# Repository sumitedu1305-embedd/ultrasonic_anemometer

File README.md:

ORTHOGONAL CONFIGURATION - NEW PCB

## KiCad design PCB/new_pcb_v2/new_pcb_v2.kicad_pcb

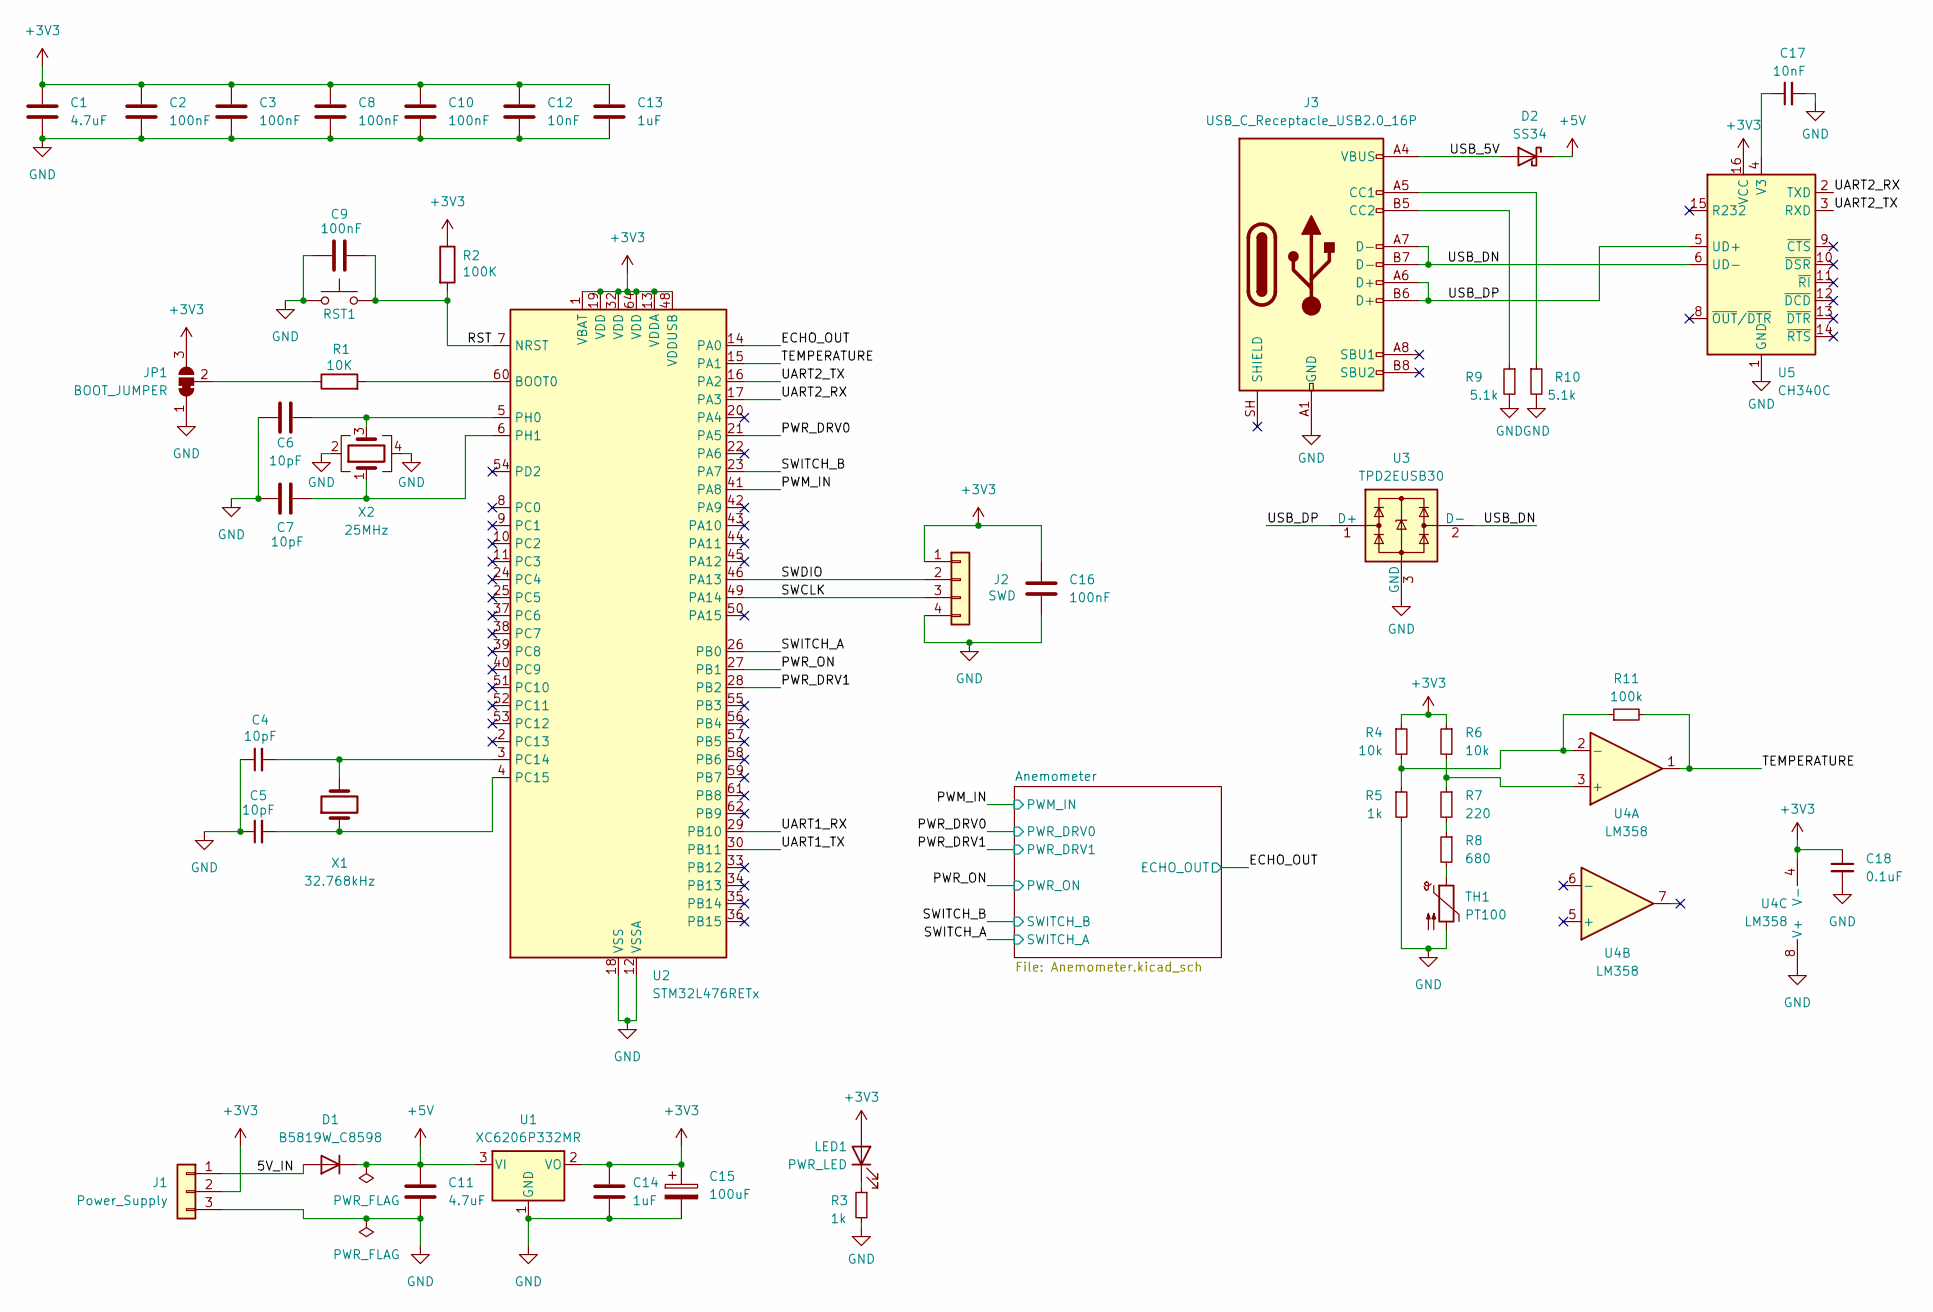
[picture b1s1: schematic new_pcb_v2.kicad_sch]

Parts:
C1, C11: 4.7uF; C_0603_1608Metric
C2, C3, C8, C9, C10, C16: 100nF; C_0402_1005Metric
C4, C5, C6, C7: 10pF; C_0402_1005Metric
C12: 10nF; C_0402_1005Metric
C13, C14: 1uF; C_0402_1005Metric
C15: 100uF; CP_EIA-3528-12_Kemet-T
C17: 10nF; C_0603_1608Metric
C18: 0.1uF; C_0603_1608Metric
D1: B5819W_C8598; D_SOD-123
D2: SS34; D_SMA
J1: Power_Supply; PinHeader_1x03_P2.54mm_Vertical
J2: SWD; PinHeader_1x04_P2.54mm_Vertical
J3: USB_C_Receptacle_USB2.0_16P; USB_C_Receptacle_G-Switch_GT-USB-7010ASV
JP1: BOOT_JUMPER; SolderJumper-3_P1.3mm_Bridged12_RoundedPad1.0x1.5mm_NumberL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
LED1: PWR_LED; LED_0603_1608Metric
R1: 10K; R_0603_1608Metric
R2: 100K; R_0603_1608Metric
R3, R5: 1k; R_0603_1608Metric
R4, R6: 10k; R_0603_1608Metric
R7: 220; R_0603_1608Metric
R8: 680; R_0603_1608Metric
R9, R10: 5.1k; R_0603_1608Metric
R11: 100k; R_0603_1608Metric
RST1: SW_Push; SW_SPST_B3U-1000P
TH1: PT100; TO-92-2
U1: XC6206P332MR; SOT-23-3
U2: STM32L476RETx; LQFP-64_10x10mm_P0.5mm
U3: TPD2EUSB30; Texas_DRT-3
U4: LM358; SO-8_3.9x4.9mm_P1.27mm
U5: CH340C; SOIC-16_3.9x9.9mm_P1.27mm
X1: 32.768kHz; Crystal_SMD_2012-2Pin_2.0x1.2mm
X2: 25MHz; Oscillator_SMD_Abracon_ASE-4Pin_3.2x2.5mm

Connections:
+3V3: C1.1, C2.1, C3.1, C8.1, C10.1, C12.1, C13.1, C14.1, C15.1, C16.1, C18.1, J1.2, J2.1, JP1.3 (B), LED1.2 (A), R2.1, R4.1, R6.1, U1.2 (VO), U2.1 (VBAT), U2.13 (VDDA), U2.19 (VDD), U2.32 (VDD), U2.48 (VDDUSB), U2.64 (VDD), U4.4 (V-), U5.16 (VCC); also elsewhere on the board
+5V: C11.1, D1.1 (K), D2.1 (K), U1.3 (VI)
/5V_IN: D1.2 (A), J1.1; also elsewhere on the board
/ECHO_OUT: U2.14 (PA0); also elsewhere on the board
/PWM_IN: U2.41 (PA8); also elsewhere on the board
/PWR_DRV0: U2.21 (PA5); also elsewhere on the board
/PWR_DRV1: U2.28 (PB2); also elsewhere on the board
/PWR_ON: U2.27 (PB1); also elsewhere on the board
/RST: C9.2, R2.2, RST1.2, U2.7 (NRST)
/SWCLK: J2.3, U2.49 (PA14); also elsewhere on the board
/SWDIO: J2.2, U2.46 (PA13); also elsewhere on the board
/SWITCH_A: U2.26 (PB0); also elsewhere on the board
/SWITCH_B: U2.23 (PA7); also elsewhere on the board
/TEMPERATURE: R11.2, U2.15 (PA1), U4.1
/UART1_RX: U2.29 (PB10)
/UART1_TX: U2.30 (PB11)
/UART2_RX: U2.17 (PA3), U5.2 (TXD)
/UART2_TX: U2.16 (PA2), U5.3 (RXD)
/USB_5V: D2.2 (A), J3.A4 (VBUS), J3.A9 (VBUS), J3.B4 (VBUS), J3.B9 (VBUS)
/USB_DN: J3.A7 (D-), J3.B7 (D-), U3.2 (D-), U5.6 (UD-)
/USB_DP: J3.A6 (D+), J3.B6 (D+), U3.1 (D+), U5.5 (UD+)
GND: C1.2, C2.2, C3.2, C4.1, C5.1, C6.1, C7.1, C8.2, C9.1, C10.2, C11.2, C12.2, C13.2, C14.2, C15.2, C16.2, C17.2, C18.2, J1.3, J2.4, J3.A1 (GND), J3.A12 (GND), J3.B1 (GND), J3.B12 (GND), JP1.1 (A), R3.2, R5.2, R9.2, R10.2, RST1.1, TH1.2, U1.1 (GND), U2.12 (VSSA), U2.18 (VSS), U2.31 (VSS), U2.47 (VSS), U2.63 (VSS), U3.3 (GND), U4.8 (V+), U5.1 (GND), X2.2, X2.4; also elsewhere on the board
unnamed: J3.A5 (CC1), R10.1
unnamed: J3.B5 (CC2), R9.1
unnamed: JP1.2 (C), R1.1
unnamed: LED1.1 (K), R3.1
unnamed: R7.2, R8.1
unnamed 49: R8.2, TH1.1; also elsewhere on the board
unnamed: R1.2, U2.60 (BOOT0)
unnamed: C4.2, U2.3 (PC14), X1.2
unnamed: C5.2, U2.4 (PC15), X1.1
unnamed: C6.2, U2.5 (PH0), X2.3
unnamed: C7.2, U2.6 (PH1), X2.1
unnamed: R6.2, R7.1, U4.3 (+)
unnamed: R4.2, R5.1, R11.1, U4.2 (-)
unnamed: C17.1, U5.4 (V3)

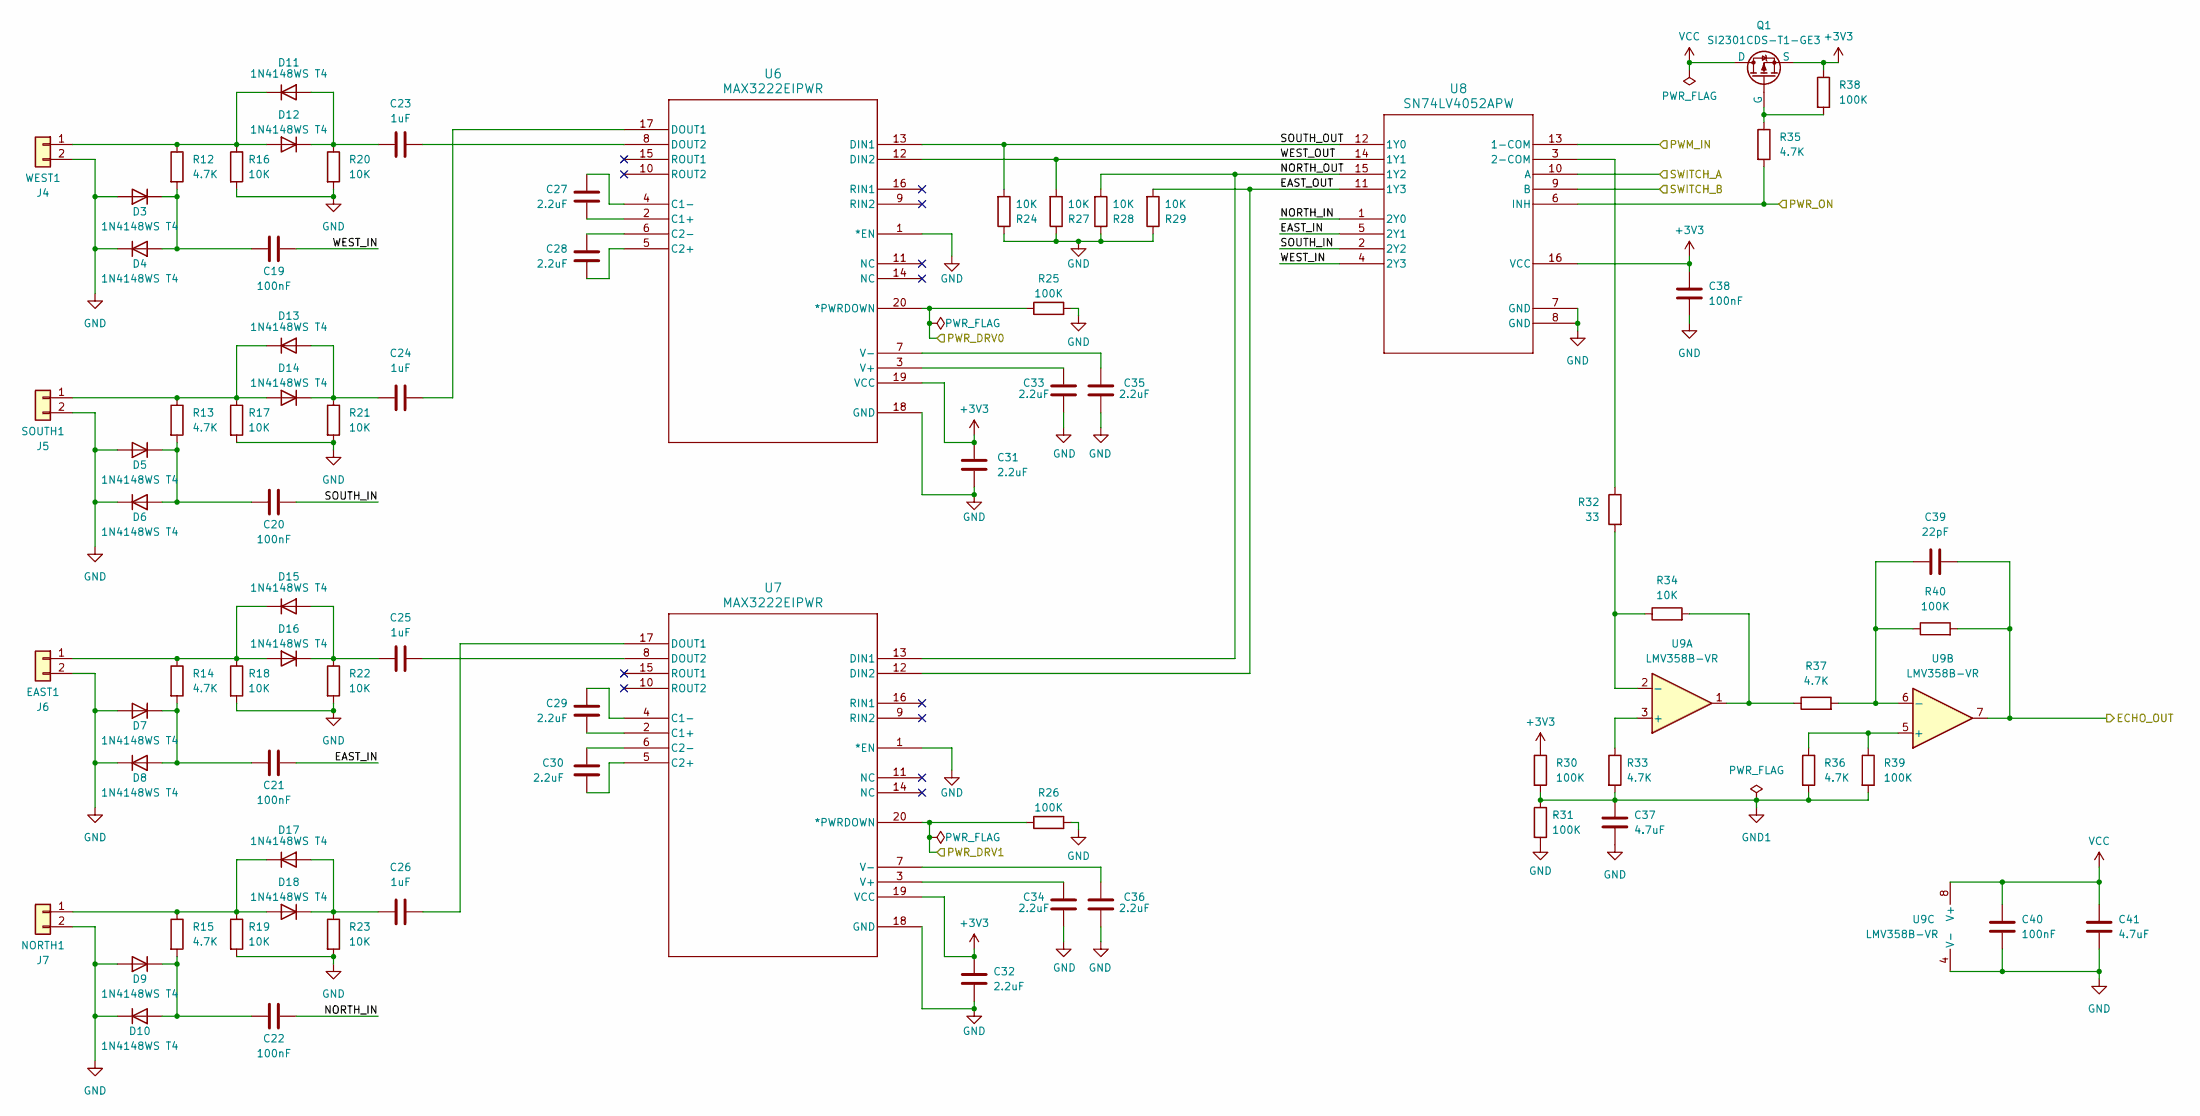
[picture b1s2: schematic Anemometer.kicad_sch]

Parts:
C19, C20, C21, C22, C40: 100nF; C_0402_1005Metric
C23, C24, C25, C26: 1uF; C_0603_1608Metric
C27, C28, C29, C30, C31, C32, C33, C34, C35, C36: 2.2uF; C_0603_1608Metric
C37: 4.7uF; C_0402_1005Metric
C38: 100nF; C_0603_1608Metric
C39: 22pF; C_0402_1005Metric
C41: 4.7uF; C_0603_1608Metric
D3, D4, D5, D6, D7, D8, D9, D10, D11, D12, D13, D14, D15, D16, D17, D18: 1N4148WS T4; D_SOD-323
J4: WEST1; JST_PH_B2B-PH-K_1x02_P2.00mm_Vertical
J5: SOUTH1; JST_PH_B2B-PH-K_1x02_P2.00mm_Vertical
J6: EAST1; JST_PH_B2B-PH-K_1x02_P2.00mm_Vertical
J7: NORTH1; JST_PH_B2B-PH-K_1x02_P2.00mm_Vertical
Q1: SI2301CDS-T1-GE3; SOT-23-3
R12, R13, R14, R15, R33, R35, R36, R37: 4.7K; R_0402_1005Metric
R16, R17, R18, R19, R20, R21, R22, R23, R24, R27, R28, R29, R34: 10K; R_0402_1005Metric
R25, R26, R30, R31, R38, R39, R40: 100K; R_0402_1005Metric
R32: 33; R_0402_1005Metric
U6, U7: MAX3222EIPWR; TSSOP-20_4.4x6.5mm_P0.65mm
U8: SN74LV4052APW; TSSOP-16_4.4x5mm_P0.65mm
U9: LMV358B-VR; MSOP-8_3x3mm_P0.65mm

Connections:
+3V3: C31.1, C32.1, C38.1, Q1.2 (S), R30.1, R38.1, U6.19 (VCC), U7.19 (VCC), U8.16 (VCC); also elsewhere on the board
/Anemometer/EAST_IN: C21.2, U8.5 (2Y1)
/Anemometer/EAST_OUT: R29.2, U7.12 (DIN2), U8.11 (1Y3)
/Anemometer/NORTH_IN: C22.2, U8.1 (2Y0)
/Anemometer/NORTH_OUT: R28.2, U7.13 (DIN1), U8.15 (1Y2)
/Anemometer/SOUTH_IN: C20.2, U8.2 (2Y2)
/Anemometer/SOUTH_OUT: R24.2, U6.13 (DIN1), U8.12 (1Y0)
/Anemometer/WEST_IN: C19.2, U8.4 (2Y3)
/Anemometer/WEST_OUT: R27.2, U6.12 (DIN2), U8.14 (1Y1)
/ECHO_OUT: C39.2, R40.2, U9.7; also elsewhere on the board
/PWM_IN: U8.13 (1-COM); also elsewhere on the board
/PWR_DRV0: R25.1, U6.20 (*PWRDOWN); also elsewhere on the board
/PWR_DRV1: R26.1, U7.20 (*PWRDOWN); also elsewhere on the board
/PWR_ON: R35.2, U8.6 (INH); also elsewhere on the board
/SWITCH_A: U8.10 (A); also elsewhere on the board
/SWITCH_B: U8.9 (B); also elsewhere on the board
GND: C31.2, C32.2, C33.1, C34.1, C35.1, C36.1, C37.2, C38.2, C40.2, C41.2, D3.2 (A), D4.1 (K), D5.2 (A), D6.1 (K), D7.2 (A), D8.1 (K), D9.2 (A), D10.1 (K), J4.2, J5.2, J6.2, J7.2, R16.2, R17.2, R18.2, R19.2, R20.2, R21.2, R22.2, R23.2, R24.1, R25.2, R26.2, R27.1, R28.1, R29.1, R31.2, U6.1 (*EN), U6.18 (GND), U7.1 (*EN), U7.18 (GND), U8.7 (GND), U8.8 (GND), U9.4 (V-); also elsewhere on the board
GND1: C37.1, R30.2, R31.1, R33.2, R36.2, R39.2
unnamed: C19.1, D3.1 (K), D4.2 (A), R12.2
unnamed: C20.1, D5.1 (K), D6.2 (A), R13.2
unnamed: C21.1, D7.1 (K), D8.2 (A), R14.2
unnamed: C22.1, D9.1 (K), D10.2 (A), R15.2
unnamed: C23.1, D11.2 (A), D12.1 (K), R20.1
unnamed 36: D11.1 (K), D12.2 (A), J4.1, R12.1, R16.1; also elsewhere on the board
unnamed: C24.1, D13.2 (A), D14.1 (K), R21.1
unnamed 38: D13.1 (K), D14.2 (A), J5.1, R13.1, R17.1; also elsewhere on the board
unnamed: C25.1, D15.2 (A), D16.1 (K), R22.1
unnamed 40: D15.1 (K), D16.2 (A), J6.1, R14.1, R18.1; also elsewhere on the board
unnamed: C26.1, D17.2 (A), D18.1 (K), R23.1
unnamed 42: D17.1 (K), D18.2 (A), J7.1, R15.1, R19.1; also elsewhere on the board
unnamed: Q1.1 (G), R35.1, R38.2
unnamed: R34.2, R37.1, U9.1
unnamed: C27.2, U6.2 (C1+)
unnamed: C27.1, U6.4 (C1-)
unnamed: C28.1, U6.5 (C2+)
unnamed: C28.2, U6.6 (C2-)
unnamed: C24.2, U6.17 (DOUT1)
unnamed: C23.2, U6.8 (DOUT2)
unnamed: C33.2, U6.3 (V+)
unnamed: C35.2, U6.7 (V-)
unnamed: C29.2, U7.2 (C1+)
unnamed: C29.1, U7.4 (C1-)
unnamed: C30.1, U7.5 (C2+)
unnamed: C30.2, U7.6 (C2-)
unnamed: C26.2, U7.17 (DOUT1)
unnamed: C25.2, U7.8 (DOUT2)
unnamed: C34.2, U7.3 (V+)
unnamed: C36.2, U7.7 (V-)
unnamed: R32.1, U8.3 (2-COM)
unnamed: R33.1, U9.3 (+)
unnamed: R32.2, R34.1, U9.2 (-)
unnamed: R36.1, R39.1, U9.5 (+)
unnamed: C39.1, R37.2, R40.1, U9.6 (-)
VCC: C40.1, C41.1, Q1.3 (D), U9.8 (V+)

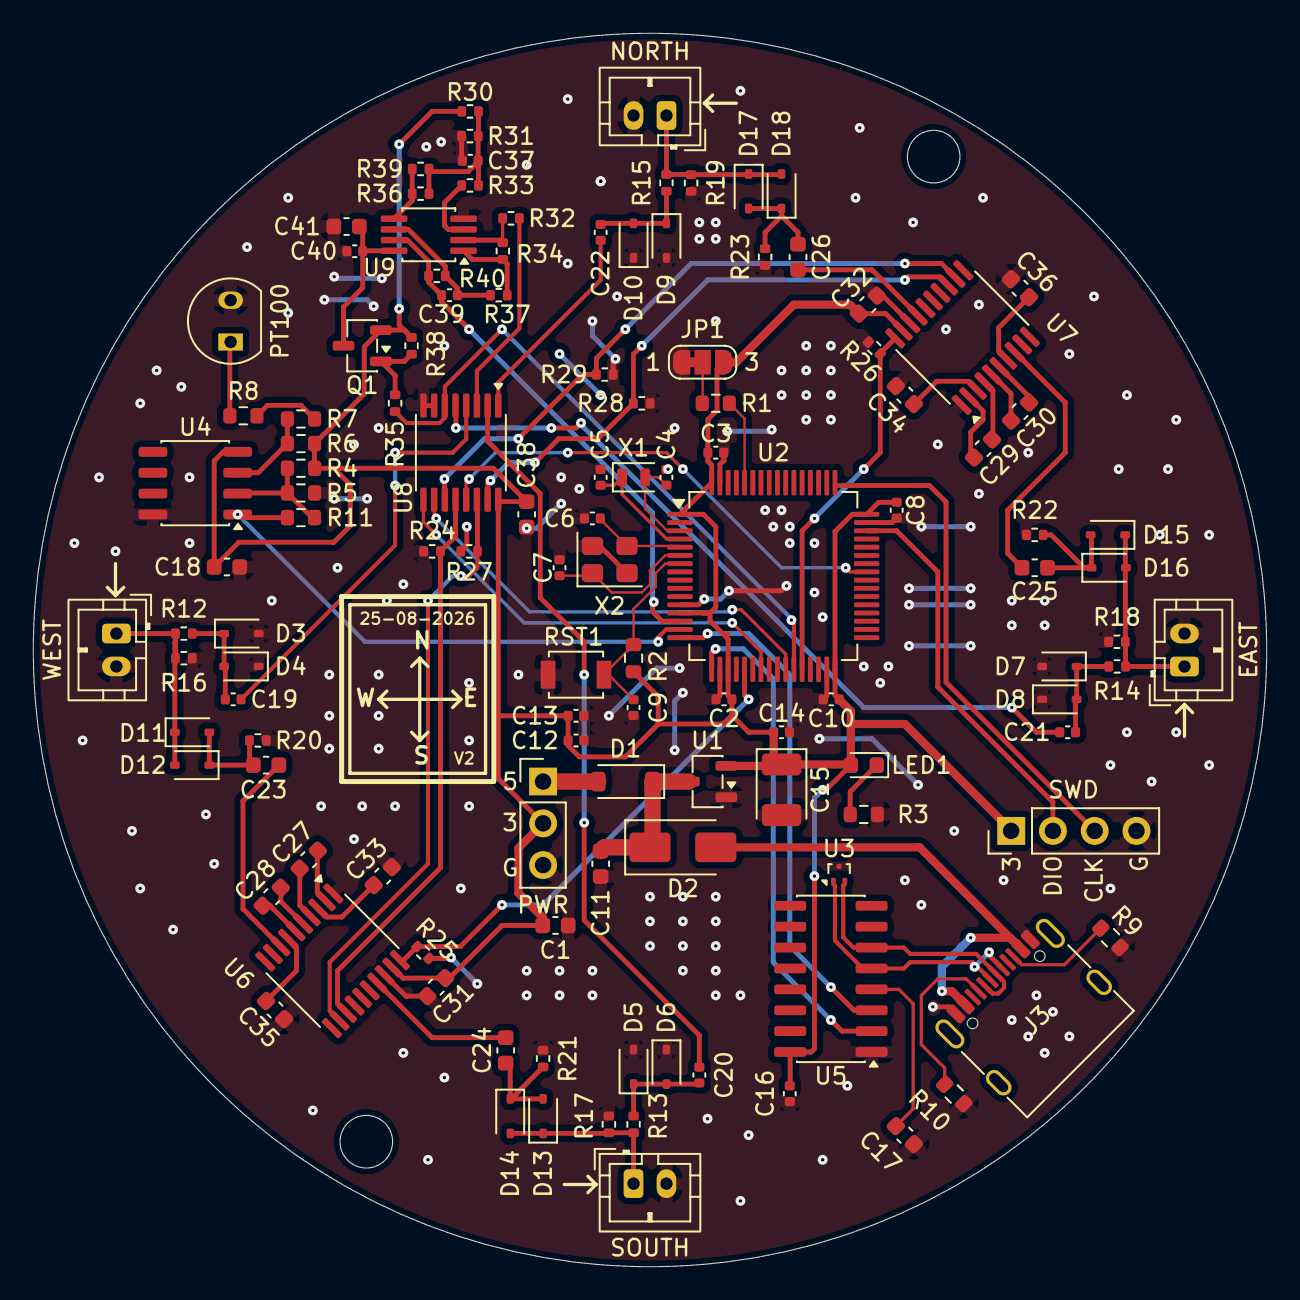
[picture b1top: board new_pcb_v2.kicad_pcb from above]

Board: 2 copper layers, 75.0 x 75.0 mm, 122 parts (0 on the bottom side), 79 nets.

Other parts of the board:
EAST: EAST1; JST_PH_B2B-PH-K_1x02_P2.00mm_Vertical
NORTH: NORTH1; JST_PH_B2B-PH-K_1x02_P2.00mm_Vertical
PT100: PT100; TO-92-2
PWR: Power_Supply; PinHeader_1x03_P2.54mm_Vertical
SOUTH: SOUTH1; JST_PH_B2B-PH-K_1x02_P2.00mm_Vertical
SWD: SWD; PinHeader_1x04_P2.54mm_Vertical
WEST: WEST1; JST_PH_B2B-PH-K_1x02_P2.00mm_Vertical

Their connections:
+3V3: PWR.2, SWD.1; also elsewhere on the board
/5V_IN: PWR.1; also elsewhere on the board
/SWCLK: SWD.3; also elsewhere on the board
/SWDIO: SWD.2; also elsewhere on the board
GND: EAST.2, NORTH.2, PT100.2, PWR.3, SOUTH.2, SWD.4, WEST.2; also elsewhere on the board
unnamed 36: WEST.1; also elsewhere on the board
unnamed 38: SOUTH.1; also elsewhere on the board
unnamed 40: EAST.1; also elsewhere on the board
unnamed 42: NORTH.1; also elsewhere on the board
unnamed 49: PT100.1; also elsewhere on the board

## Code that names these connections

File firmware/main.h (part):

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#define CALIB_SAMPLES           100

// peripheral - port
#define PWR_DRV0_GPIO_Port      GPIOA
#define ECHO_OUT_GPIO_Port      GPIOA
#define LED2_GPIO_Port          GPIOC
#define LED1_GPIO_Port          GPIOC
#define LED3_GPIO_Port          GPIOC
#define PWR_DRV1_GPIO_Port      GPIOB
#define SWITCH_A_GPIO_Port      GPIOB
#define PWR_ON_GPIO_Port        GPIOB
#define SWITCH_B_GPIO_Port      GPIOA

// peripheral - pin
#define PWR_DRV0_Pin    5
#define ECHO_OUT_Pin    0
#define LED2_Pin        3
#define LED1_Pin        2
#define LED3_Pin        6
#define PWR_DRV1_Pin    2
#define SWITCH_A_Pin    0
#define PWR_ON_Pin      1
#define SWITCH_B_Pin    7

// gpio mux output configs 
#define south_out()                                            \
        do                                                     \
        {                                                      \
                GPIO_Set(SWITCH_A_GPIO_Port, SWITCH_A_Pin, 0); \
                GPIO_Set(SWITCH_B_GPIO_Port, SWITCH_B_Pin, 0); \
                GPIO_Set(PWR_DRV0_GPIO_Port, PWR_DRV0_Pin, 1); \
                GPIO_Set(PWR_DRV1_GPIO_Port, PWR_DRV1_Pin, 0); \
        } while (0)
#define north_out()                                            \
        do                                                     \
        {                                                      \
                GPIO_Set(SWITCH_A_GPIO_Port, SWITCH_A_Pin, 0); \
                GPIO_Set(SWITCH_B_GPIO_Port, SWITCH_B_Pin, 1); \
                GPIO_Set(PWR_DRV0_GPIO_Port, PWR_DRV0_Pin, 0); \
                GPIO_Set(PWR_DRV1_GPIO_Port, PWR_DRV1_Pin, 1); \
        } while (0)
#define west_out()                                             \
        do                                                     \
        {                                                      \
                GPIO_Set(SWITCH_A_GPIO_Port, SWITCH_A_Pin, 1); \
                GPIO_Set(SWITCH_B_GPIO_Port, SWITCH_B_Pin, 0); \
                GPIO_Set(PWR_DRV0_GPIO_Port, PWR_DRV0_Pin, 1); \
                GPIO_Set(PWR_DRV1_GPIO_Port, PWR_DRV1_Pin, 0); \
        } while (0)
#define east_out()                                             \
        do                                                     \
        {                                                      \
                GPIO_Set(SWITCH_A_GPIO_Port, SWITCH_A_Pin, 1); \
                GPIO_Set(SWITCH_B_GPIO_Port, SWITCH_B_Pin, 1); \
                GPIO_Set(PWR_DRV0_GPIO_Port, PWR_DRV0_Pin, 0); \
                GPIO_Set(PWR_DRV1_GPIO_Port, PWR_DRV1_Pin, 1); \
        } while (0)


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
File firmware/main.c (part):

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
    delay_ms(10);

    GPIO_Set(PWR_ON_GPIO_Port, PWR_ON_Pin, 0);

    delay_ms(10);

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    RCC_AHB2ENR |= (1 << 0);       
    RCC_AHB2ENR |= (1 << 13);     

    // PA1 as Analog Mode
    GPIO_MODER(GPIOA) |= (3 << (1 * 2));    // Set PA1 to 11 (Analog)
    GPIO_PUPDR(GPIOA) &= ~(3 << (1 * 2));   // No pull-up/pull-down
    GPIO_ASCR(GPIOA)  |= (1 << 1);

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    while (ADC_CR(ADC2) & (1 << 31));       // Wait for calibration to finish
    ADC_SQR1(ADC2) &= ~(0xF << 0);          // L = 0 (1 conversion per sequence)
    ADC_SQR1(ADC2) &= ~(0x1F << 6);         // Clear SQ1
    ADC_SQR1(ADC2) |= (6 << 6);             // SQ1 = Channel 6 (PA1)
    ADC_SMPR1(ADC2) |= (7 << (3 * 6));   
    ADC_CFGR(ADC2) |= (1 << 13);            // CONT = 1 (Continuous Conversion Mode)
    ADC_CFGR(ADC2) |= (1 << 1);             // DMACFG = 1 (DMA Circular Mode)
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    RCC_AHB1ENR |= (1 << 0);
    RCC_APB1ENR1 |= (1 << 17);

    // PA2 TX
    GPIO_MODER(GPIOA) &= ~(3 << (2 * 2));
    GPIO_MODER(GPIOA) |= (2 << (2 * 2));
    GPIO_OSPEEDR(GPIOA) |= (3 << (2 * 2));
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    RCC_AHB2ENR |= (1 << 0);  // GPIOA clock

    GPIO_MODER(GPIOA) &= ~(3 << (8 * 2));
    GPIO_MODER(GPIOA) |= (2 << (8 * 2)); // AF mode, PA8
    GPIO_AFRH(GPIOA) &= ~(0xF << ((8 - 8) * 4));
    GPIO_AFRH(GPIOA) |= (1 << ((8 - 8) * 4)); // AF1 (TIM1_CH1)
    GPIO_OTYPER(GPIOA) &= ~(1 << 8);
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}
void GPIO_Init()
{
    GPIO_Config(PWR_ON_GPIO_Port, PWR_ON_Pin);
    GPIO_Config(PWR_DRV0_GPIO_Port, PWR_DRV0_Pin);
    GPIO_Config(PWR_DRV1_GPIO_Port, PWR_DRV1_Pin);
    GPIO_Config(SWITCH_A_GPIO_Port, SWITCH_A_Pin);
    GPIO_Config(SWITCH_B_GPIO_Port, SWITCH_B_Pin);
    GPIO_Config(LED1_GPIO_Port, LED1_Pin);
    GPIO_Config(LED2_GPIO_Port, LED2_Pin);
    GPIO_Config(LED3_GPIO_Port, LED3_Pin);
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
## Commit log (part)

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2026-04-09 Initial commit: firmware + python UART handling
2026-04-09 Added print statement for debugging in wind_0804.py
2026-04-09 2nd update
2026-04-10 new day
2026-04-10 works fair right now
2026-04-10 smoothen + outliers filters added
2026-04-10 now 4 transducers
2026-04-10 small updates 2 sensors though
2026-04-10 final 2 sensor update : smoothening
2026-04-10 2 sensors : mean changed to median due to more variations
2026-04-10 read frame changed sync + sequence mattered (sequence one was not attained at first
2026-04-10 4 Sensors : initial commit
2026-04-13 4 sensors 2nd commmit not working though
2026-04-13 changed firmware to reduce buffer size as there was problem in plotting (stops randomly) but didnt solved it. though keeping buffer smaller as more silent zone is not required. now improving data aqu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
2026-04-13 python file resolved works fine now no changes to processing though
2026-04-13 fixed wrong vectors for compass draw
2026-04-13 fair results : calibration code still remaining
2026-04-13 calibration added : press c to calibrate
2026-04-13 fixes : calibration and buffer sizes
2026-04-13 Working : orthogonal configuration
2026-04-14 final commit for branch 1 orthogonal conifguration : added README
2026-04-14 initial commit to new branch for reflector based design
2026-04-14 inital commit nothing changed
2026-04-14 firmware tweaked (delay buffer size changed for similar behavior)
2026-04-14 delay set to 300us
2026-04-14 nothing new
2026-04-15 no changes : clear status
2026-04-16 no changes : status cleared
2026-04-16 improvements : changed dc offset removal method to only use signal in silent zone (better stability)
2026-04-20 no changes : just added macros switching to main branch
2026-04-20 no changes : switching v reflect branch
2026-04-20 Stop tracking local Keil build and config files
2026-04-27 fixes : had to increase ring delay (cap issue (slew rate maybe)) - to accomodate this buffere decrease and other params changed (silent zone, delays in firmware, buffer size, etc)
2026-04-27 working : 35mm 80degrees approx fair result. now final product based files
2026-04-29 Working : change in assembly after this
2026-04-29 no changes : made new branch for final produce
2026-05-04 no changes : Code made more readable .c,h,py. Moreover the gitignore changes to remove user and app specific output files. Added requirements to ignore adding .venv to the project repo
2026-05-04 no changes : remove .venv from git tracking
2026-05-05 no changes
2026-05-05 untrack ignored files
2026-05-06 working : changes applied. willing to add signal processing in the firmware itself
2026-05-13 main branch : sab bandh ho gaya lol
2026-05-13 added git ignore
2026-05-13 applying .gitignore
2026-05-26 working : fare working. assymetry may still needs to be solved. calibration without tunnel is difficult. also added signal processing in c but never integreted it so avoid it right now. signal proces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
2026-05-28 changes : added temperature integration code to it. ye to be tested though
2026-05-28 changed gitignore to remove .vscode too
2026-06-04 working : temperature working and integrated. assymetry code also removed and manual calibrated ratios are added. fare operation though. yet to be tested along side reflector one
2026-06-09 Fixes : Changed the TX_pulses code to remove the phantom interrupt firring
2026-06-16 working : fair results, assymetry needs to be calibrated, temperature acquistation added
